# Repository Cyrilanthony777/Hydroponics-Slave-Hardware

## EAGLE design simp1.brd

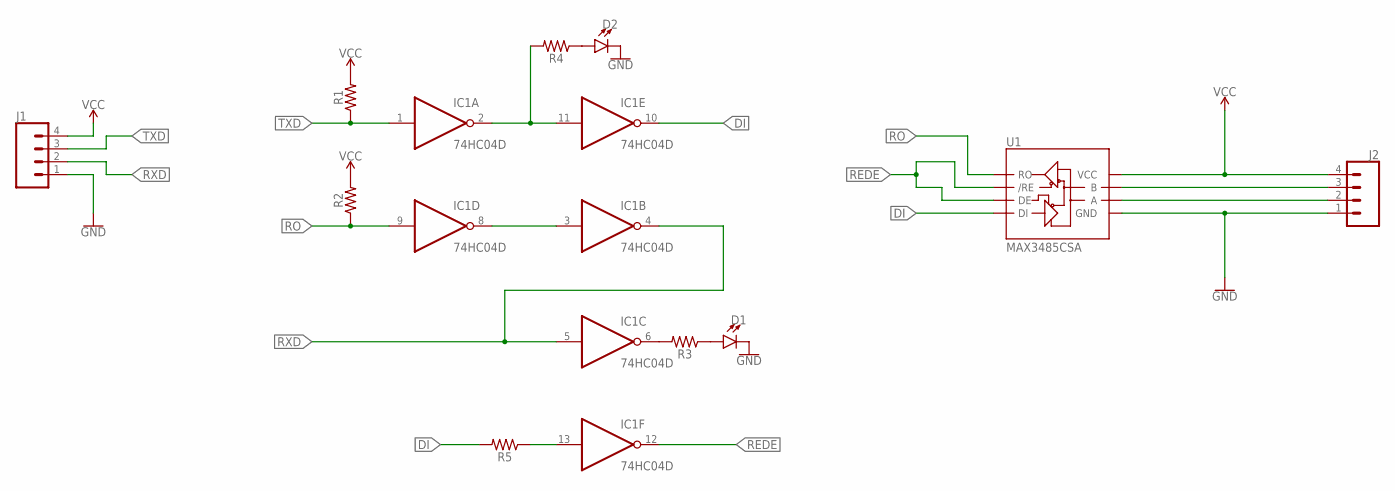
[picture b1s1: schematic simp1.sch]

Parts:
D1, D2: LED0603; LED-0603
IC1: 74HC04D; SO14
J1, J2: CONN_04PTH; 1X04
R1, R2, R3, R4, R5: 0603
U1: MAX3485CSA; SO08

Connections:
DI: IC1.10 (O), R5.2, U1.4 (DI)
GND: D1.C, D2.C, IC1.7 (GND), J1.1, J2.1, U1.5 (GND)
unnamed: IC1.2 (O), IC1.11 (I), R4.2
unnamed: J2.3, U1.7 (B)
unnamed: J2.2, U1.6 (A)
unnamed: IC1.3 (I), IC1.8 (O)
unnamed: D2.A, R4.1
unnamed: IC1.6 (O), R3.2
unnamed: D1.A, R3.1
unnamed: IC1.13 (I), R5.1
REDE: IC1.12 (O), U1.2 (/RE), U1.3 (DE)
RO: IC1.9 (I), R2.1, U1.1 (RO)
RXD: IC1.4 (O), IC1.5 (I), J1.2
TXD: IC1.1 (I), J1.3, R1.1
VCC: IC1.14 (VCC), J1.4, J2.4, R1.2, R2.2, U1.8 (VCC)

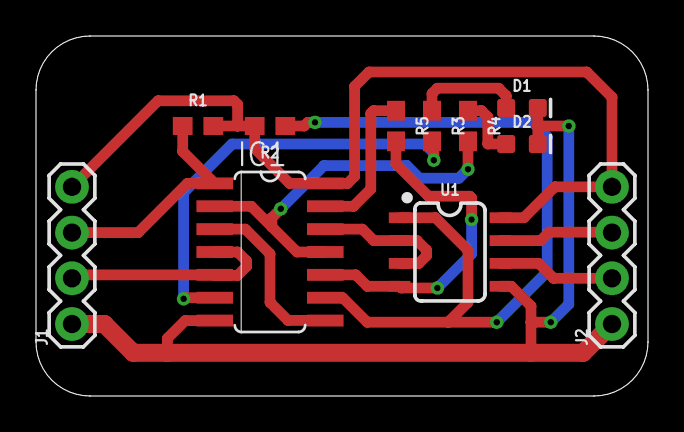
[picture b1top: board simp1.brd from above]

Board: 2 copper layers, 34.0 x 20.0 mm, 11 parts (0 on the bottom side), 15 nets.

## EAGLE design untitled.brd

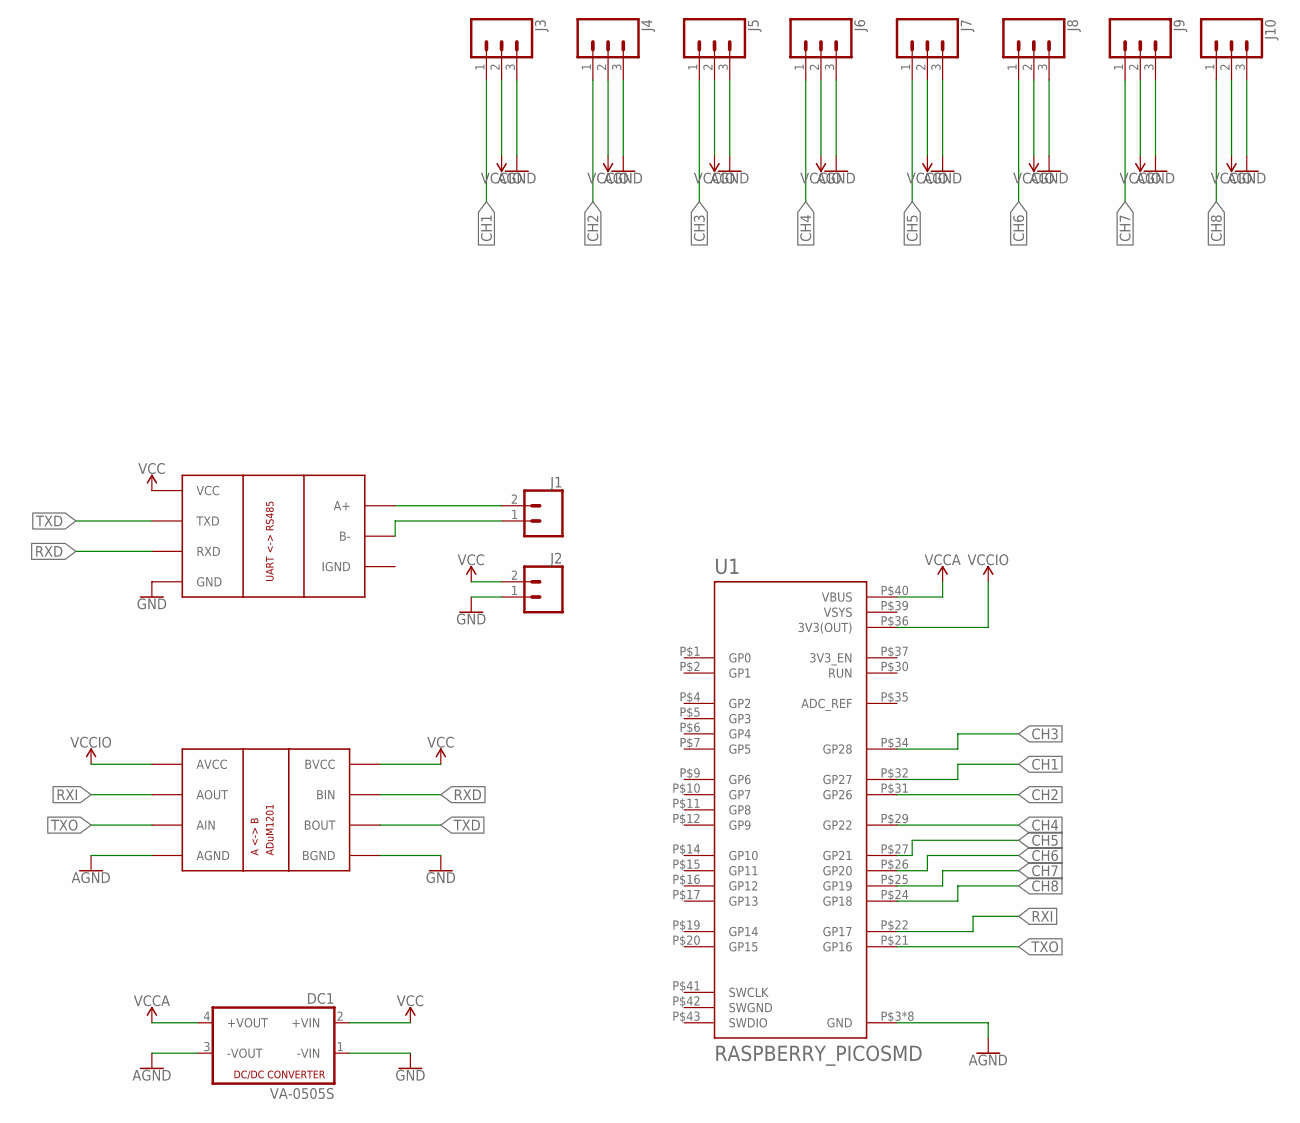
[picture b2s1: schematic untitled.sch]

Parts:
DC1: VA-0505S; 4SIL
J1, J2: CONN_025MM; SCREWTERMINAL-5MM-2
J3, J4, J5, J6, J7, J8, J9, J10: CONN_03; 1X03
U1: RASPBERRY_PICOSMD; PICO-PKG-SMD
U$1: RS485-UART-CONVERTER; RS485_MODULE
U$2: ADUM1201; SO8

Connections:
AGND: DC1.3 (-VOUT), J3.3, J4.3, J5.3, J6.3, J7.3, J8.3, J9.3, J10.3, U1.P$3 (GND), U1.P$8 (GND), U1.P$13 (GND), U1.P$18 (GND), U1.P$23 (GND), U1.P$28 (GND), U1.P$33 (GND), U1.P$38 (GND), U$2.4 (AGND)
CH1: J3.1, U1.P$32 (GP27)
CH2: J4.1, U1.P$31 (GP26)
CH3: J5.1, U1.P$34 (GP28)
CH4: J6.1, U1.P$29 (GP22)
CH5: J7.1, U1.P$27 (GP21)
CH6: J8.1, U1.P$26 (GP20)
CH7: J9.1, U1.P$25 (GP19)
CH8: J10.1, U1.P$24 (GP18)
GND: DC1.1 (-VIN), J2.1, U$1.GND, U$2.5 (BGND)
unnamed: J1.2, U$1.A+
unnamed: J1.1, U$1.B-
RXD: U$1.RXD, U$2.7 (BIN)
RXI: U1.P$22 (GP17), U$2.2 (AOUT)
SWGND: U1.P$42 (SWGND)
TXD: U$1.TXD, U$2.6 (BOUT)
TXO: U1.P$21 (GP16), U$2.3 (AIN)
VCC: DC1.2 (+VIN), J2.2, U$1.VCC, U$2.8 (BVCC)
VCCA: DC1.4 (+VOUT), U1.P$40 (VBUS)
VCCIO: J3.2, J4.2, J5.2, J6.2, J7.2, J8.2, J9.2, J10.2, U1.P$36 (3V3(OUT)), U$2.1 (AVCC)
VSYS: U1.P$39 (VSYS)

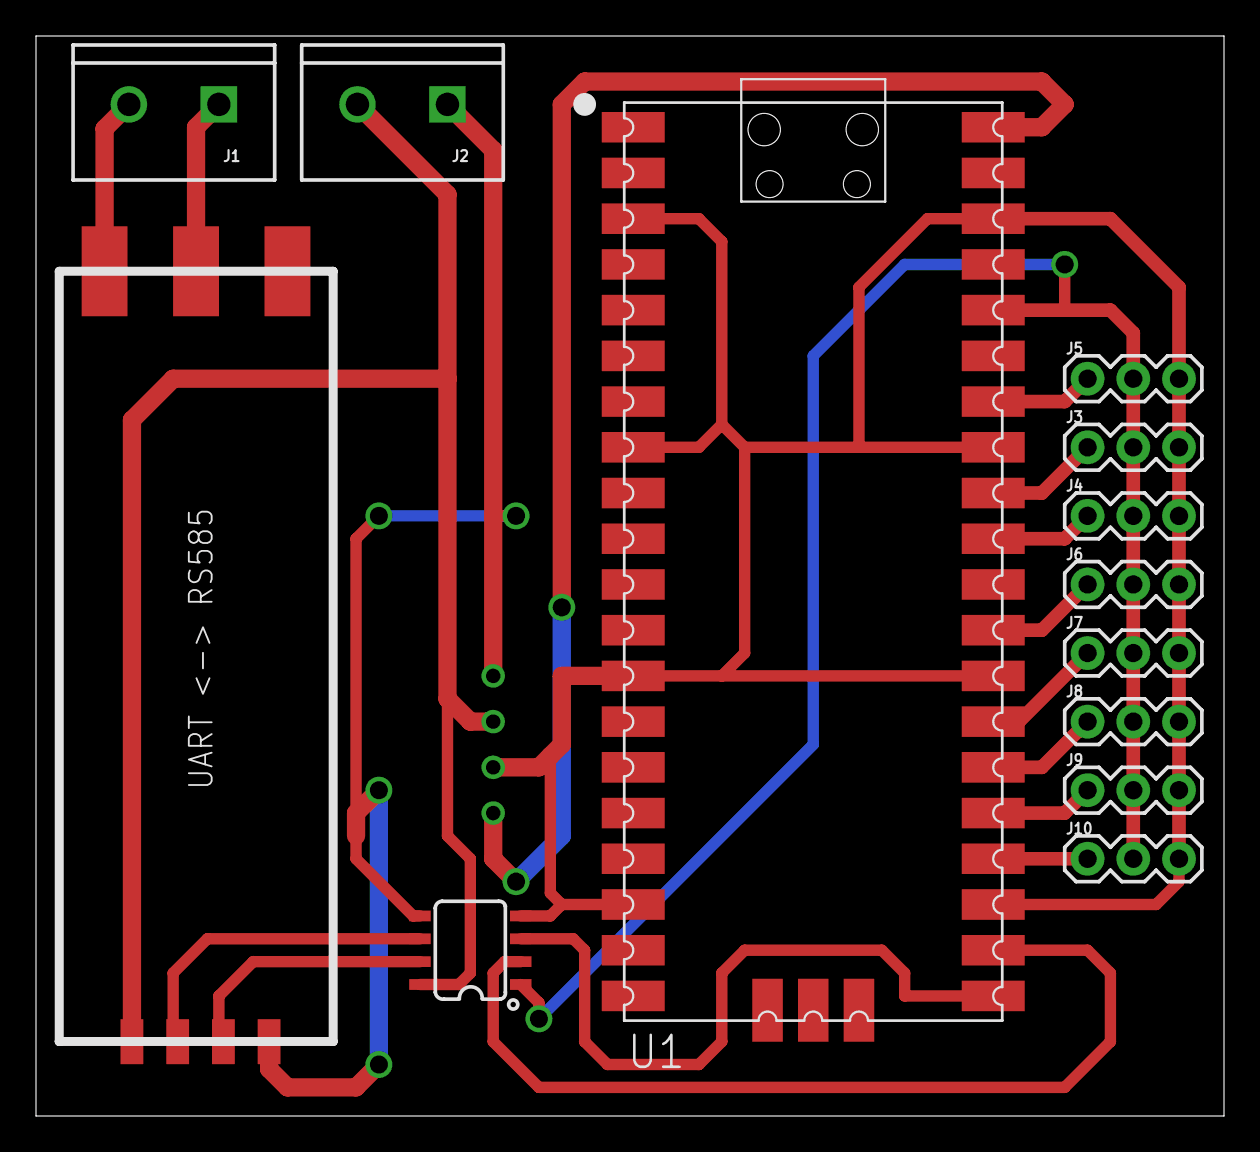
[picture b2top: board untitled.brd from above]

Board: 2 copper layers, 66.0 x 60.0 mm, 14 parts (1 on the bottom side), 19 nets.

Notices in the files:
parts and their libraries:
SparkFun-LED: Licensing: Creative Commons ShareAlike 4.0 International - https://creativecommons.org/licenses/by-sa/4.0
